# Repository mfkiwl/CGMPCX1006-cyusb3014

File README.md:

# CGMPCX1006
Amplifier Board PCB Project

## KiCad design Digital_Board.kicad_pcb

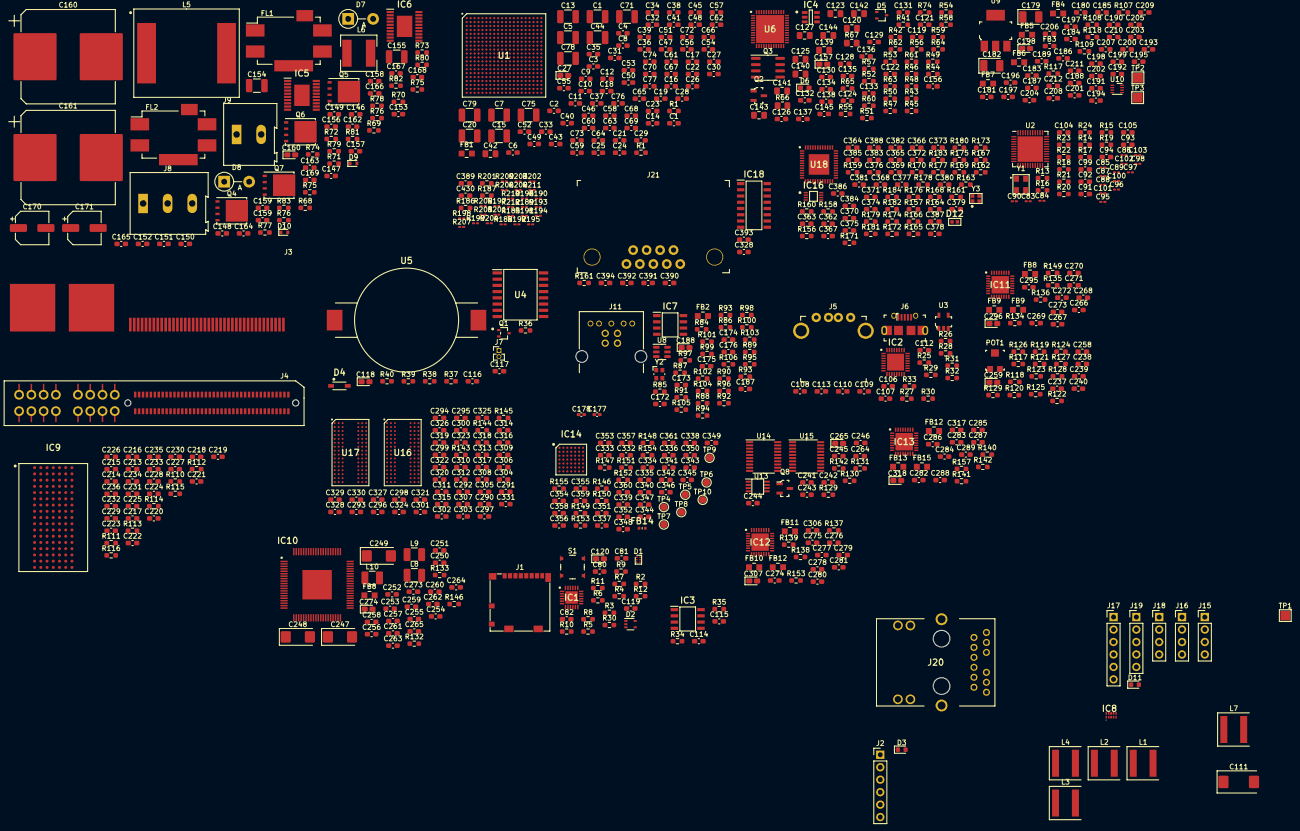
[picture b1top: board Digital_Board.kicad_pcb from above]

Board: 2 copper layers, 761 parts (0 on the bottom side), 493 nets, no tracks yet.

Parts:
C1, C5, C7, C13, C15, C20, C71, C75, C78, C79: 100uF; C_1210_3225Metric_Pad1.33x2.70mm_HandSolder
C1#2, C119, C156#2, C159#2, C175, C187#2, C197#2, C258#2, C264#2, C273#2, C295#2, C306#2, C317#2: C_Small; C_0603_1608Metric_Pad1.08x0.95mm_HandSolder
C2, C3, C6, C9, C11, C14, C16, C18, C21, C22, C27, C34, C41, C57, C62, C63, C67, C68, C69, C70, C72, C73, C74, C76, C77, C113, C119#2, C180, C186: 4.7uF; C_0603_1608Metric_Pad1.08x0.95mm_HandSolder
C4, C8, C10, C12, C17, C19, C23, C24, C25, C26, C28, C29, C30, C31, C32, C33, C35, C36, C37, C38, C39, C40, C43, C45, C46, C47, C48, C49, C50, C51, C52, C53, C54, C55, C56, C58, C59, C60, C61, C64, C65, C66, C314, C315, C318, C319, C322, C323: 470nF; C_0603_1608Metric_Pad1.08x0.95mm_HandSolder
C27#2, C120, C157#2, C160#2, C188#2, C198#2, C259#2, C265#2, C274#2, C296#2, C307#2, C318#2: C_Polarized_Small; CP_EIA-1608-10_AVX-L_Pad1.25x1.05mm_HandSolder
C42, C120#2, C123, C125, C127: 10uF; C_0805_2012Metric_Pad1.18x1.45mm_HandSolder
C44: 47uF; C_1210_3225Metric_Pad1.33x2.70mm_HandSolder
C80, C81, C82, C106, C107, C108, C109, C110, C114, C117, C124, C135, C136, C137, C138, C146, C147, C152, C153, C164, C165, C174, C176, C181, C183, C184, C185, C187, C189, C190, C191, C193, C194, C195, C196, C198, C199, C200, C201, C202, C203, C204, C205, C211, C213, C214, C215, C216, C217, C218, C219, C220, C221, C222, C223, C224, C225, C226, C227, C228, C229, C230, C231, C232, C233, C234, C235, C236, C237, C241, C242, C243, C244, C245, C246, C250, C251, C252, C253, C254, C255, C256, C257, C258, C259, C260, C261, C262, C263, C264, C265, C266, C270, C271, C272, C273, C274, C278, C279, C280, C281, C282, C286, C287, C288, C289, C389, C390, C391, C392, C393, C394: 100nF; C_0603_1608Metric_Pad1.08x0.95mm_HandSolder
C83, C84, C85, C86, C87, C88, C89, C90, C95, C96, C97, C98, C100, C101, C102, C103: 100nF; C_0201_0603Metric_Pad0.64x0.40mm_HandSolder
C91, C92, C93, C94, C99, C104, C105, C126, C128, C134, C145, C166, C167, C335, C338, C339, C343, C362, C363, C364, C365, C366, C367, C368: 1uF; C_0603_1608Metric_Pad1.08x0.95mm_HandSolder
C111: 150uF; CP_EIA-7343-30_AVX-N
C112: 1nF; C_0603_1608Metric_Pad1.08x0.95mm_HandSolder
C115: 30pF; C_0603_1608Metric_Pad1.08x0.95mm_HandSolder
C116, C346, C369, C370, C371, C372, C373, C374, C375, C376, C377, C378, C379, C380, C384, C385, C386, C387, C388: 0.1uF; C_0603_1608Metric_Pad1.08x0.95mm_HandSolder
C118: 1uF; CP_EIA-1608-10_AVX-L_Pad1.25x1.05mm_HandSolder
C121, C133: 1uFF; C_0603_1608Metric_Pad1.08x0.95mm_HandSolder
C122: 2.2nF; C_0603_1608Metric_Pad1.08x0.95mm_HandSolder
C129, C130, C131, C132: 2.7nF; C_0603_1608Metric_Pad1.08x0.95mm_HandSolder
C139, C140, C141, C142: 47uF; C_0805_2012Metric_Pad1.18x1.45mm_HandSolder
C143, C144: 22uF; C_0805_2012Metric_Pad1.18x1.45mm_HandSolder
C148, C149, C150, C151, C188, C192, C197: 2.2uF; C_0603_1608Metric_Pad1.08x0.95mm_HandSolder
C154, C155: 1uF; C_1210_3225Metric_Pad1.33x2.70mm_HandSolder
C156: 560pF; C_0603_1608Metric_Pad1.08x0.95mm_HandSolder
C157: 200pF; C_0603_1608Metric_Pad1.08x0.95mm_HandSolder
C158, C159, C353: 33nF; C_0603_1608Metric_Pad1.08x0.95mm_HandSolder
C160, C161: 330uF; CP_Elec_18x17.5
C162, C163: 10pF; C_0603_1608Metric_Pad1.08x0.95mm_HandSolder
C168: 220pF; C_0603_1608Metric_Pad1.08x0.95mm_HandSolder
C169: 270pF; C_0603_1608Metric_Pad1.08x0.95mm_HandSolder
C170, C171: 47uF; CP_Elec_6.3x5.9
C172, C173: 7pF; C_0603_1608Metric_Pad1.08x0.95mm_HandSolder
C177, C178: 100nF; C_0402_1005Metric_Pad0.74x0.62mm_HandSolder
C179, C182: 10uF; CP_EIA-3528-21_Kemet-B_Pad1.50x2.35mm_HandSolder
C206, C207, C208, C209, C210, C212, C292, C297, C330, C331: 10nF; C_0603_1608Metric_Pad1.08x0.95mm_HandSolder
C238, C240: 900pF; C_0603_1608Metric_Pad1.08x0.95mm_HandSolder
C239: 4.7pF; C_0603_1608Metric_Pad1.08x0.95mm_HandSolder
C247, C248, C249: 100uF; CP_EIA-6032-28_Kemet-C
C267, C268, C269, C275, C276, C277, C283, C284, C285, C332, C341, C342, C345, C347, C348, C350, C383: 10uF; C_0603_1608Metric_Pad1.08x0.95mm_HandSolder
C290, C291, C293, C294, C295, C296, C298, C299, C300, C301, C302, C303, C304, C305, C306, C307, C308, C309, C310, C311, C312, C313, C316, C317, C320, C321, C324, C325, C326, C327, C328, C329: 47nF; C_0603_1608Metric_Pad1.08x0.95mm_HandSolder
C328#2, C430: aaaa; C_0603_1608Metric_Pad1.08x0.95mm_HandSolder
C333, C334, C336, C337, C340, C344, C349, C351: 47uF; C_0603_1608Metric_Pad1.08x0.95mm_HandSolder
C352: 15nF; C_0603_1608Metric_Pad1.08x0.95mm_HandSolder
C354, C355, C356, C357, C358, C359, C360, C361: 4.7nF; C_0603_1608Metric_Pad1.08x0.95mm_HandSolder
C381, C382: 8pF; C_0603_1608Metric_Pad1.08x0.95mm_HandSolder
D1: PESD5V0L5UF; SOT-886
D2: SP0504BAJT; SOT-353_SC-70-5
D3, D11: LED_Small; LED_0603_1608Metric
D4: B0520LW-7-F; SOD3716X145N
D5: BAS16W; SOT-323_SC-70
D6: LED; LED_0603_1608Metric_Pad1.05x0.95mm_HandSolder
D7, D8: SAC50; D_DO-15_P5.08mm_Vertical_AnodeUp
D9, D10: BAS516; D_SOD-523
D12: GREEN; LEDC1006X25N
FB1, FB4, FB5, FB6, FB7, FB8, FB8#2, FB9, FB9#2, FB10, FB11, FB12, FB12#2, FB13, FB15: MPZ2012S601AT000; 0805
FB2: BLM21PG221SN1D; 0805
FB3: BLM18SG121TZ1D; L_0603_1608Metric_Pad1.05x0.95mm_HandSolder
FB14: 1.2A; BEADC1005X55N
FL1: BNX025; Filter_Murata_BNX025
FL2: BNX024; Filter_Murata_BNX024
IC1: TXS02612RTWR; QFN50P400X400X80-25N-D
IC2: USB3320C-EZK; QFN50P500X500X100-33N-D
IC3, IC7: M24M02-DRMN6TP; SOIC127P600X175-8N
IC4: ADR127BUJZ-REEL7; SOT95P280X100-6N
IC5, IC6: LM5116MHX_NOPB; SOP65P640X110-21N
IC8: TPD4E05U06QDQARQ1; DQA_R-PUSON-N10_
IC9: CY7C1062GE30-10BGXI; BGA119C127P7X17_1400X2200X240
IC10: AD9726BSVZ; QFP50P1400X1400X120-81N
IC11, IC12, IC13: LTC2387CUH-18#PBF; QFN50P500X500X80-33N-D
IC14: LTM8078IY#PBF; BGA49C80P7X7_625X625X242
IC16: SN74LVC3G14DCUR; SOP50P310X90-8N
IC18: SP3232EEN-L_TR; SOIC127P600X175-16N
J1: 104031-0811; microSD_HC_Molex_104031-0811
J2, J17: Conn_01x06; PinHeader_1x06_P2.54mm_Vertical
J3: BoardEdge_of_HSEC8-140-01-L-PV-4-1
J4: BoardEdge_of_HSEC8-140-01-L-PV-4-1; HSEC8-140-01-L-PV-4-1
J5: UE27AC54100; USB_A_Female_UE27AC54100
J6: 0475890001; USB_Micro_AB_Female_0475890001
J7: Conn_01x02; PinHeader_1x02_P1.27mm_Vertical
J8: Screw_Terminal_01x03; TerminalBlock_Altech_AK300-3_P5.00mm
J9: Screw_Terminal_01x02; TerminalBlock_Altech_AK300-2_P5.00mm
J11: USB3_B; GSB3211311WEU
J15, J16, J18: Conn_01x04; PinHeader_1x04_P2.54mm_Vertical
J19: Conn_01x05; PinHeader_1x05_P2.54mm_Vertical
J20: RJMG2012211A0FR
J21: 5747840-6; DSUB-9_Jack_5747840-3
L1: 3.3uH; L_Coilcraft_XAL60xx_6.36x6.56mm
L2, L7: 1uH; L_Coilcraft_XAL60xx_6.36x6.56mm
L3, L4: 6.8uH; L_Coilcraft_XAL60xx_6.36x6.56mm
L5: 3.3uH; IHLP6767GZER3R3M01
L6: 2.2uH; L_Coilcraft_XxL7070
L8, L9, L10: 10uH; L_1210_3225Metric_Pad1.42x2.65mm_HandSolder
POT1: TC33X-2-103E; Trimpot_3.8mmx3.6mm_TC33X-2-103E
Q1: MCH3481-TL-W; SOT65P270X085-3N
Q2, Q8: FDV301N; SOT-23-3
Q3: FDS9926A; SOIC-8_3.9x4.9mm_P1.27mm
Q4, Q6: CSD18534Q5A; TDSON-8-1
Q5, Q7: CSD18540Q5B; TDSON-8-1
R1, R3, R31, R32, R34, R51, R54, R99, R102, R110, R111, R112, R161, R162, R163: 0; R_0603_1608Metric_Pad0.98x0.95mm_HandSolder
R1#2, R30#2, R74#2, R75#2, R76#2, R93#2, R117#2, R118#2, R129#2, R142#2, R146#2, R149#2, R153#2, R157#2: R_Small_US; R_0603_1608Metric_Pad0.98x0.95mm_HandSolder
R2, R9, R10, R15, R18, R42, R48, R107, R144: 4.7K; R_0603_1608Metric_Pad0.98x0.95mm_HandSolder
R4, R6, R13, R14, R16, R17, R19, R20, R40, R41, R44, R84, R85, R100, R113, R114, R115, R129, R130, R134, R135, R136, R137, R138, R139, R140, R141, R142, R148, R149, R159: 10K; R_0603_1608Metric_Pad0.98x0.95mm_HandSolder
R5, R105: 200; R_0603_1608Metric_Pad0.98x0.95mm_HandSolder
R7, R8, R21, R22, R23, R24, R122, R123, R127, R128: 100; R_0603_1608Metric_Pad0.98x0.95mm_HandSolder
R11, R12: 220; R_0603_1608Metric_Pad0.98x0.95mm_HandSolder
R25, R153: 1.5K; R_0603_1608Metric_Pad0.98x0.95mm_HandSolder
R26, R43: 8.06K; R_0603_1608Metric_Pad0.98x0.95mm_HandSolder
R27, R29, R45, R101: 100K; R_0603_1608Metric_Pad0.98x0.95mm_HandSolder
R28, R30, R36, R37, R38, R39, R120, R121, R126, R133, R146, R147: 1K; R_0603_1608Metric_Pad0.98x0.95mm_HandSolder
R33, R74, R75, R119, R154, R155: 1M; R_0603_1608Metric_Pad0.98x0.95mm_HandSolder
R35: 4K; R_0603_1608Metric_Pad0.98x0.95mm_HandSolder
R46, R131: 680; R_0603_1608Metric_Pad0.98x0.95mm_HandSolder
R47, R77: 66.5K; R_0603_1608Metric_Pad0.98x0.95mm_HandSolder
R49: 8.87K; R_0603_1608Metric_Pad0.98x0.95mm_HandSolder
R50: 20K; R_0603_1608Metric_Pad0.98x0.95mm_HandSolder
R52, R53: 47K; R_0603_1608Metric_Pad0.98x0.95mm_HandSolder
R55: 39.2K; R_0603_1608Metric_Pad0.98x0.95mm_HandSolder
R56: 12.7K 1%; R_0603_1608Metric_Pad0.98x0.95mm_HandSolder
R57: 4.99K 1%; R_0603_1608Metric_Pad0.98x0.95mm_HandSolder
R58: 1.91K 1%; R_0603_1608Metric_Pad0.98x0.95mm_HandSolder
R59: 2.49K 1%; R_0603_1608Metric_Pad0.98x0.95mm_HandSolder
R60: 19.6K 1%; R_0603_1608Metric_Pad0.98x0.95mm_HandSolder
R61: 10.2K; R_0603_1608Metric_Pad0.98x0.95mm_HandSolder
R62: 31.6K 1%; R_0603_1608Metric_Pad0.98x0.95mm_HandSolder
R63: 28.7K 1%; R_0603_1608Metric_Pad0.98x0.95mm_HandSolder
R64: 10.2K 1%; R_0603_1608Metric_Pad0.98x0.95mm_HandSolder
R65: 10K 1%; R_0603_1608Metric_Pad0.98x0.95mm_HandSolder
R66, R67: 0R; R_0805_2012Metric_Pad1.20x1.40mm_HandSolder
R68, R70: 52.3K; R_0603_1608Metric_Pad0.98x0.95mm_HandSolder
R69, R71: 1.74K; R_0603_1608Metric_Pad0.98x0.95mm_HandSolder
R72, R81: 9.76K; R_0603_1608Metric_Pad0.98x0.95mm_HandSolder
R73: 5.23K; R_0603_1608Metric_Pad0.98x0.95mm_HandSolder
R76: 133K; R_0603_1608Metric_Pad0.98x0.95mm_HandSolder
R78: 2mOhm; R_0603_1608Metric_Pad0.98x0.95mm_HandSolder
R79: 6mOhm; R_0603_1608Metric_Pad0.98x0.95mm_HandSolder
R80: 86.6K; R_0603_1608Metric_Pad0.98x0.95mm_HandSolder
R82: 32.4K; R_0603_1608Metric_Pad0.98x0.95mm_HandSolder
R83: 10.4K; R_0603_1608Metric_Pad0.98x0.95mm_HandSolder
R86, R87, R88, R89, R90, R91, R92, R93, R94, R95, R96, R97, R98, R157, R160: 22; R_0603_1608Metric_Pad0.98x0.95mm_HandSolder
R103, R104, R116, R132: 2K; R_0603_1608Metric_Pad0.98x0.95mm_HandSolder
R106: 6.04K; R_0603_1608Metric_Pad0.98x0.95mm_HandSolder
R108, R109: 0R; R_0603_1608Metric_Pad0.98x0.95mm_HandSolder
R117, R118, R124, R125: Select; R_0603_1608Metric_Pad0.98x0.95mm_HandSolder
R143, R145: 240; R_0603_1608Metric_Pad0.98x0.95mm_HandSolder
R150: 28K; R_0603_1608Metric_Pad0.98x0.95mm_HandSolder
R151: 665K; R_0603_1608Metric_Pad0.98x0.95mm_HandSolder
R152: 118K; R_0603_1608Metric_Pad0.98x0.95mm_HandSolder
R156: 11K; R_0603_1608Metric_Pad0.98x0.95mm_HandSolder
R158: 2.2K; R_0603_1608Metric_Pad0.98x0.95mm_HandSolder
R161#2, R201#2: AAA; R_0603_1608Metric_Pad0.98x0.95mm_HandSolder
R164, R181, R182: 420; R_0603_1608Metric_Pad0.98x0.95mm_HandSolder
R165, R166, R167, R168, R169, R170, R171, R172, R173, R174, R175, R176, R177, R178, R179, R180, R183, R184: 2.49K; R_0603_1608Metric_Pad0.98x0.95mm_HandSolder
R185: 40.2; R_0201_0603Metric_Pad0.64x0.40mm_HandSolder
R186, R187: 80.6; R_0603_1608Metric_Pad0.98x0.95mm_HandSolder
R188, R189, R190, R191, R192, R193, R194, R195, R196, R197, R198, R199, R200, R201, R202, R203, R204, R205, R206, R207, R208, R209, R210, R212: 10; R_0201_0603Metric_Pad0.64x0.40mm_HandSolder
R211: 80.6; R_0201_0603Metric_Pad0.64x0.40mm_HandSolder
S1: TL3315NF100Q; Switch_Tactile_SMD_4.5x4.5mm_TL3315NF160Q
TP1, TP2, TP3: TestPoint; TestPoint_Pad_2.0x2.0mm
TP4, TP5, TP6, TP7, TP8, TP9, TP10: TestPoint; TestPoint_Pad_D1.5mm
U1: XA7Z020-1CLG400Q; BGA400C80P20X20_1700X1700X160
U2: Si5344A-D; QFN-44-1EP_7x7mm_P0.5mm_EP5.2x5.2mm
U3: TPS2051BDBVR; SOT-753
U4: DS3231S#; SOIC127P1032X265-16N
U5: BU2032SM-HD-G
U6: ADP5052ACPZ-R7; QFN50P700X700X80-49N-D
U8: WE-TVS-82400102; SOT-23-6
U9: NCP1117ST33T3G; SOT-223
U10: MIC23150; TDFN-8-2x2mm_P0.5mm
U13: TCA9406DC; SOP65P425X315X130-8N
U14, U15: TXS0108EPW; TSSOP-20_4.4x6.5mm_P0.65mm
U16, U17: AS4C256M16D3LC-12BCN; BGA96C80P9X16_750X1350X120
U18: DP83869HMRGZT; QFN50P700X700X100-49N-D
Y1: CX3225SB48000D0FPJC1; OSCCC320X250X60N
Y2: 19.2Mhz; Crystal_SMD_Abracon_ABM10-4Pin_2.5x2.0mm
Y3: XRCGE25M000FBA1AR0

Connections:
5VUSB3: C179.1, C180.1, FB3.1, R102.1, R107.2, U8.5, U9.3, U10.6, U10.7
+48VIN: C155.1, D7.1, FL2.1, J4.81, J4.82, J8.3
+48VIN_F: C146.1, C147.1, C148.1, C149.1, C150.1, C151.1, C152.1, C153.1, C161.1, FL2.2, IC5.1, IC6.1, Q4.5, Q6.5, R68.1, R70.1, R74.1, R75.1
-48VIN: J3.81, J3.82, J8.1
/12V: C120#2.1, C123.1, C125.1, C127.1, C160.1, C170.1, D4.1, FL1.2, IC5.10, J7.1, L5.1, R80.1, U6.4, U6.9, U6.24, U6.25, U6.35, U6.36
/48V_12V_Buck/EXT_12VIN: C154.1, D8.1, FL1.1, J9.2
/48V_12V_Buck/EXT_12VIN_G: C154.2, D8.2, FL1.3, J9.1
/ADC/ADC_CNV_N: IC11.27, IC12.27, IC13.27
/ADC/ADC_CNV_P: IC11.28, IC12.28, IC13.28
/BTB_Connector/ADC1_CLK_N: J4.53, U1.W9
/BTB_Connector/ADC1_CLK_P: J4.51, U1.W10
/BTB_Connector/ADC1_DA_N: J4.65, U1.Y11
/BTB_Connector/ADC1_DA_P: J4.63, U1.W11
/BTB_Connector/ADC1_DCO_N: J4.59, U1.U8
/BTB_Connector/ADC1_DCO_P: J4.57, U1.U9
/BTB_Connector/ADC2_CLK_N: J4.71, U1.U5
/BTB_Connector/ADC2_CLK_P: J4.69, U1.T5
/BTB_Connector/ADC2_DA_N: J4.76, U1.V10
/BTB_Connector/ADC2_DA_P: J4.78, U1.V11
/BTB_Connector/ADC2_DCO_N: J4.77, U1.Y13
/BTB_Connector/ADC2_DCO_P: J4.75, U1.Y12
/BTB_Connector/ADC3_CLK_N: J4.70, U1.V7
/BTB_Connector/ADC3_CLK_P: J4.72, U1.U7
/BTB_Connector/ADC3_DA_N: J4.58, U1.W6
/BTB_Connector/ADC3_DA_P: J4.60, U1.V6
/BTB_Connector/ADC3_DCO_N: J4.64, U1.Y8
/BTB_Connector/ADC3_DCO_P: J4.66, U1.Y9
/BTB_Connector/ADC_CNV_N: J4.52, U1.W8
/BTB_Connector/ADC_CNV_P: J4.54, U1.V8
/BTB_Connector/FDAC_DB0_N: J4.45, U1.P20
/BTB_Connector/FDAC_DB0_P: J4.47, U1.N20
/BTB_Connector/FDAC_DB1_N: J4.39, U1.U15
/BTB_Connector/FDAC_DB1_P: J4.41, U1.U14
/BTB_Connector/FDAC_DB2_N: J4.33, U1.H15
/BTB_Connector/FDAC_DB2_P: J4.35, U1.G15
/BTB_Connector/FDAC_DB3_N: J4.27, U1.R17
/BTB_Connector/FDAC_DB3_P: J4.29, U1.R16
/BTB_Connector/FDAC_DB4_N: J4.21, U1.R14
/BTB_Connector/FDAC_DB4_P: J4.23, U1.P14
/BTB_Connector/FDAC_DB5_N: J4.15, U1.P16
/BTB_Connector/FDAC_DB5_P: J4.17, U1.P15
/BTB_Connector/FDAC_DB6_N: J4.9, U1.P18
/BTB_Connector/FDAC_DB6_P: J4.11, U1.N17
/BTB_Connector/FDAC_DB7_N: J4.3, U1.W19
/BTB_Connector/FDAC_DB7_P: J4.5, U1.W18
/BTB_Connector/FDAC_DB8_N: J4.48, U1.W13
/BTB_Connector/FDAC_DB8_P: J4.46, U1.V12
/BTB_Connector/FDAC_DB9_N: J4.42, U1.T10
/BTB_Connector/FDAC_DB9_P: J4.40, U1.T11
/BTB_Connector/FDAC_DB10_N: J4.36, U1.J16
/BTB_Connector/FDAC_DB10_P: J4.34, U1.K16
/BTB_Connector/FDAC_DB11_N: J4.30, U1.M15
/BTB_Connector/FDAC_DB11_P: J4.28, U1.M14
/BTB_Connector/FDAC_DB12_N: J4.24, U1.F17
/BTB_Connector/FDAC_DB12_P: J4.22, U1.F16
/BTB_Connector/FDAC_DB13_N: J4.18, U1.D18
/BTB_Connector/FDAC_DB13_P: J4.16, U1.E17
/BTB_Connector/FDAC_DB14_N: J4.12, U1.A20
/BTB_Connector/FDAC_DB14_P: J4.10, U1.B19
/BTB_Connector/FDAC_DB15_N: J4.6, U1.B20
/BTB_Connector/FDAC_DB15_P: J4.4, U1.C20
/Clock_Gen/CLK_A0: R19.2, R20.1, U2.16
/Clock_Gen/CLK_A1: R16.2, R17.1, U2.15
/Clock_Gen/CLK_A_N: C84.1, R21.2, U2.44
/Clock_Gen/CLK_A_P: C83.1, R21.1, U2.43
/Clock_Gen/CLK_B_N: C86.1, R22.2, U2.2
/Clock_Gen/CLK_B_P: C85.1, R22.1, U2.1
/Clock_Gen/CLK_C_N: C88.1, R23.2, U2.11
/Clock_Gen/CLK_C_P: C87.1, R23.1, U2.10
/Clock_Gen/CLK_D_N: C90.1, R24.2, U2.42
/Clock_Gen/CLK_D_P: C89.1, R24.1, U2.41
/Clock_Gen/CLK_I2C_SEL: R13.2, R14.1, U2.38
/EEPROM/EEPROM_SDA: C115.1, IC3.5, R35.2
/Ethernet/ETH_INT_PDWN: R158.2, U18.44
/Ethernet/ETH_MDC: U1.C10, U18.42
/Ethernet/ETH_MDIO: R153.1, U1.C11, U18.41
/Ethernet/ETH_PHY_CONN/ETH_A_N: J20.8, U18.2
/Ethernet/ETH_PHY_CONN/ETH_A_P: J20.9, U18.1
/Ethernet/ETH_PHY_CONN/ETH_B_N: J20.3, U18.5
/Ethernet/ETH_PHY_CONN/ETH_B_P: J20.2, U18.4
/Ethernet/ETH_PHY_CONN/ETH_C_N: J20.4, U18.8
/Ethernet/ETH_PHY_CONN/ETH_C_P: J20.5, U18.7
/Ethernet/ETH_PHY_CONN/ETH_D_N: J20.11, U18.11
/Ethernet/ETH_PHY_CONN/ETH_D_P: J20.10, U18.10
/Ethernet/ETH_PHY_CONN/ETH_GPIO_0: IC16.6, R163.1, R175.2, R176.1, TP6.1, U18.45
/Ethernet/ETH_PHY_CONN/ETH_JTAG_CLK: TP7.1, U18.21
/Ethernet/ETH_PHY_CONN/ETH_JTAG_TDI: TP8.1, U18.24
/Ethernet/ETH_PHY_CONN/ETH_JTAG_TDO: R157.1, R157.2, R169.2, R170.1, TP9.1, U18.22
/Ethernet/ETH_PHY_CONN/ETH_JTAG_TMS: TP10.1, U18.23
/Ethernet/ETH_PHY_CONN/LED_0: IC16.1, R161.1, R171.2, R172.1, U18.47
/Ethernet/ETH_PHY_CONN/LED_1: IC16.3, R162.1, R173.2, R174.1, U18.46
/Ethernet/ETH_PHY_CONN/LED_P_0: IC16.7, J20.13, R161.2
/Ethernet/ETH_PHY_CONN/LED_P_1: IC16.5, J20.15, R162.2
/Ethernet/ETH_PHY_CONN/LED_P_2: D12.1, IC16.2, R163.2
/Ethernet/ETH_PHY_CONN/RX_D0: R179.2, R180.1
/Ethernet/ETH_PHY_CONN/RX_D1: R183.2, R184.1
/Ethernet/ETH_PHY_CONN/RX_D2: R165.2, R166.1
/Ethernet/ETH_PHY_CONN/RX_D3: R167.2, R168.1
/Ethernet/ETH_RESETn: R159.2, R160.1, U18.43
/Ethernet/ETH_RX_CLK: U1.B17, U18.32
/Ethernet/ETH_RX_CTRL: R177.2, R178.1, U1.D13, U18.38
/Ethernet/ETH_TX_CLK: U1.A19, U18.29
/Ethernet/ETH_TX_CTRL: U1.F14, U18.37
/Ext_Analog/AN0_N: C238.1, R123.1
/Ext_Analog/AN0_P: C238.2, R122.1
/Ext_Analog/AN1_N: C240.1, R128.1
/Ext_Analog/AN1_P: C240.2, R127.1
/FDAC_CLKIN_N: C100.1, J3.75
/FDAC_CLKIN_P: C95.1, J3.77
/FPGA_Banks/DAC_DCLK_IN_N: J3.69, U1.H17
/FPGA_Banks/DAC_DCLK_IN_P: J3.71, U1.H16
/FPGA_Banks/DAC_DCLK_OUT_N: J3.63, U1.K18
/FPGA_Banks/DAC_DCLK_OUT_P: J3.65, U1.K17
/FPGA_Banks/DDR3_A0: R202.1, U16.N3, U17.N3
/FPGA_Banks/DDR3_A1: R201.1, U16.P7, U17.P7
/FPGA_Banks/DDR3_A2: R200.1, U16.P3, U17.P3
/FPGA_Banks/DDR3_A3: R199.1, U16.N2, U17.N2
/FPGA_Banks/DDR3_A4: R198.1, U16.P8, U17.P8
/FPGA_Banks/DDR3_A5: R197.1, U16.P2, U17.P2
/FPGA_Banks/DDR3_A6: R196.1, U16.R8, U17.R8
/FPGA_Banks/DDR3_A7: R195.1, U16.R2, U17.R2
/FPGA_Banks/DDR3_A8: R194.1, U16.T8, U17.T8
/FPGA_Banks/DDR3_A9: R193.1, U16.R3, U17.R3
/FPGA_Banks/DDR3_A10: R192.1, U16.L7, U17.L7
/FPGA_Banks/DDR3_A11: R191.1, U16.R7, U17.R7
/FPGA_Banks/DDR3_A12: R190.1, U16.N7, U17.N7
/FPGA_Banks/DDR3_A13: R189.1, U16.T3, U17.T3
/FPGA_Banks/DDR3_A14: R188.1, U16.T7, U17.T7
/FPGA_Banks/DDR3_BA0: R205.1, U16.M2, U17.M2
/FPGA_Banks/DDR3_BA1: R204.1, U16.N8, U17.N8
/FPGA_Banks/DDR3_BA2: R203.1, U16.M3, U17.M3
/FPGA_Banks/DDR3_CAS: R207.1, U16.K3, U17.K3
/FPGA_Banks/DDR3_CKE0: R210.1, U16.K9, U17.K9
/FPGA_Banks/DDR3_CK_N: R211.2, U1.M2, U16.K7, U17.K7
/FPGA_Banks/DDR3_CK_P: R211.1, U1.L2, U16.J7, U17.J7
/FPGA_Banks/DDR3_CS: R208.1, U16.L2, U17.L2
/FPGA_Banks/DDR3_D0: U1.E3, U16.E3
/FPGA_Banks/DDR3_D1: U1.H2, U16.F7
/FPGA_Banks/DDR3_D2: U1.E2, U16.F2
/FPGA_Banks/DDR3_D3: U1.G3, U16.F8
/FPGA_Banks/DDR3_D4: U1.J1, U16.H3
/FPGA_Banks/DDR3_D5: U1.H3, U16.H8
/FPGA_Banks/DDR3_D6: U1.J3, U16.G2
/FPGA_Banks/DDR3_D7: U1.H1, U16.H7
/FPGA_Banks/DDR3_D8: U1.D3, U16.D7
/FPGA_Banks/DDR3_D9: U1.E1, U16.C3
/FPGA_Banks/DDR3_D10: U1.C1, U16.C8
/FPGA_Banks/DDR3_D11: U1.C3, U16.C2
/FPGA_Banks/DDR3_D12: U1.B3, U16.A7
/FPGA_Banks/DDR3_D13: U1.A2, U16.A2
/FPGA_Banks/DDR3_D14: U1.D1, U16.B8
/FPGA_Banks/DDR3_D15: U1.A4, U16.A3
/FPGA_Banks/DDR3_D16: U1.U4, U17.E3
/FPGA_Banks/DDR3_D17: U1.T4, U17.F7
/FPGA_Banks/DDR3_D18: U1.U3, U17.F2
/FPGA_Banks/DDR3_D19: U1.R1, U17.F8
/FPGA_Banks/DDR3_D20: U1.R3, U17.H3
/FPGA_Banks/DDR3_D21: U1.P3, U17.H8
/FPGA_Banks/DDR3_D22: U1.U2, U17.G2
/FPGA_Banks/DDR3_D23: U1.P1, U17.H7
/FPGA_Banks/DDR3_D24: U1.V2, U17.D7
/FPGA_Banks/DDR3_D25: U1.V3, U17.C3
/FPGA_Banks/DDR3_D26: U1.W3, U17.C8
/FPGA_Banks/DDR3_D27: U1.V1, U17.C2
/FPGA_Banks/DDR3_D28: U1.Y2, U17.A7
/FPGA_Banks/DDR3_D29: U1.Y3, U17.A2
/FPGA_Banks/DDR3_D30: U1.W1, U17.B8
/FPGA_Banks/DDR3_D31: U1.Y4, U17.A3
/FPGA_Banks/DDR3_DM0: U1.F1, U16.E7
/FPGA_Banks/DDR3_DM1: U1.A1, U16.D3
/FPGA_Banks/DDR3_DM2: U1.T1, U17.E7
/FPGA_Banks/DDR3_DM3: U1.Y1, U17.D3
/FPGA_Banks/DDR3_DQS0_N: U1.F2, U16.G3
/FPGA_Banks/DDR3_DQS0_P: U1.G2, U16.F3
/FPGA_Banks/DDR3_DQS1_N: U1.B2, U16.B7
/FPGA_Banks/DDR3_DQS1_P: U1.C2, U16.C7
/FPGA_Banks/DDR3_DQS2_N: U1.T2, U17.G3
/FPGA_Banks/DDR3_DQS2_P: U1.R2, U17.F3
/FPGA_Banks/DDR3_DQS3_N: U1.W4, U17.B7
/FPGA_Banks/DDR3_DQS3_P: U1.W5, U17.C7
/FPGA_Banks/DDR3_ODT0: R212.1, U16.K1, U17.K1
/FPGA_Banks/DDR3_RAS: R206.1, U16.J3, U17.J3
/FPGA_Banks/DDR3_RESET: R144.1, U1.B4, U16.T2, U17.T2
/FPGA_Banks/DDR3_VREF: C292.1, C297.1, C330.1, C331.1, C389.2, U1.H6, U1.P6, U16.H1, U16.M8, U17.H1, U17.M8
/FPGA_Banks/DDR3_WE: R209.1, U16.L3, U17.L3
/FPGA_Banks/ETH_RX_D0: U1.D11, U18.33
/FPGA_Banks/ETH_RX_D1: U1.A16, U18.34
/FPGA_Banks/ETH_RX_D2: U1.F15, U18.35
/FPGA_Banks/ETH_RX_D3: U1.A15, U18.36
/FPGA_Banks/ETH_TX_D0: U1.E14, U18.28
/FPGA_Banks/ETH_TX_D1: U1.B18, U18.27
/FPGA_Banks/ETH_TX_D2: U1.D10, U18.26
/FPGA_Banks/ETH_TX_D3: U1.A17, U18.25
/FPGA_Banks/FX3_PMOD0: R99.1, U1.Y16
/FPGA_Banks/FX3_PMOD1: R85.1, U1.Y17
/FPGA_Banks/USB2_CLK: IC2.1, R27.1, U1.A11
/FPGA_Banks/USB2_DATA0: IC2.3, U1.A14
/FPGA_Banks/USB2_DATA1: IC2.4, U1.D15
/FPGA_Banks/USB2_DATA2: IC2.5, U1.A12
/FPGA_Banks/USB2_DATA3: IC2.6, U1.F12
/FPGA_Banks/USB2_DATA4: IC2.7, U1.C16
/FPGA_Banks/USB2_DATA5: IC2.9, U1.A10
/FPGA_Banks/USB2_DATA6: IC2.10, U1.E13
/FPGA_Banks/USB2_DATA7: IC2.13, U1.C18
/FPGA_Banks/USB2_DIR: IC2.31, U1.C13
/FPGA_Banks/USB2_NXT: IC2.2, U1.E16
/FPGA_Banks/USB2_OC: R30.1, U1.U13, U3.3
/FPGA_Banks/USB2_RESTN: IC2.27, R25.2, U1.D16
/FPGA_Banks/USB2_STP: IC2.29, U1.C15
/FPGA_Config/ESD_CLK: IC1.19, J1.5
/FPGA_Config/ESD_CMD: IC1.20, J1.3
/FPGA_Config/ESD_DAT0: IC1.18, J1.7
/FPGA_Config/ESD_DAT1: IC1.16, J1.8
/FPGA_Config/ESD_DAT2: IC1.23, J1.1
/FPGA_Config/ESD_DAT3: IC1.22, J1.2
/FPGA_Config/SD_CD: D1.1, R4.2
/FPGA_Config/TCK_JTAG: D2.5, J2.4, U1.F9
/FPGA_Config/TDI_JTAG: D2.3, J2.2, U1.G6
/FPGA_Config/TDO_JTAG: D2.4, J2.3, U1.F6
/FPGA_Config/TMS_JTAG: D2.1, J2.1, U1.J6
/FPGA_Config/VP: R6.2, R7.1, U1.K9
/I2C2_SCL: R36.2, U4.16
/I2C2_SDA: R15.2, R37.2, U2.13, U4.15, U13.5
/I2C_SCL: R18.2, U2.14, U13.4
/LED_Comm/CAN_H: J18.3, U15.20
/LED_Comm/CAN_L: J18.4, U15.18
/LED_Comm/LCD_RESET: J19.1, U15.17
/LED_Comm/LCD_RX: J19.4, U15.15
/LED_Comm/LCD_TX: J19.3, U15.16
/LED_Comm/SCL: J16.4, U13.1
/LED_Comm/SDA: J16.3, U13.8
/LED_Comm/SPI_CLK: J17.5, U14.13
/LED_Comm/SPI_MISO: J17.3, U14.15
/LED_Comm/SPI_MOSI: J17.4, U14.14
/LED_Comm/SPI_SS: J17.6, U14.12
/LED_Comm/UART_RX: J15.4, U14.18
/LED_Comm/UART_TX: J15.3, U14.20
/Power_Supply/EN2: R41.1, R42.2, U6.23
/Power_Supply/VREG: R51.2, R54.2, U6.43
/RS232_Port/RS232_RX_IN1: IC18.13, J21.4
/RS232_Port/RS232_RX_IN2: IC18.8, J21.8
/RS232_Port/RS232_TX_OUT1: IC18.14, J21.7
/RS232_Port/RS232_TX_OUT2: IC18.7, J21.3
/RTC_FAN/RTC_OSC_OUT: R39.2, U4.1
/RTC_FAN/RTC_RST: TP1.1, U4.4
/RTC_FAN/RTC_SQW: R38.2, U4.3
/USB2/USB2_3V3: C109.1, IC2.20, IC2.21
/USB2/USB2_5V0: C113.1, J5.1, J6.1, R28.2, R31.1, R32.1
/USB2/USB2_D_N: IC2.19, J5.2, J6.2
/USB2/USB2_D_P: IC2.18, J5.3, J6.3
/USB2/USB2_ID: IC2.23, J6.4
/USB2/USB2_SHIELD: C112.2, J5.SH, J6.SH, R33.2
/USB3/CTL0: R86.2, R110.2
/USB3/CTL1: R92.2, R111.2
/USB3/CTL2: R87.2, R112.2
/USB3/CTL5: IC9.A6, R94.2
/USB3/CTL6: IC9.A5, R89.2
/USB3/CTL7: IC9.A4, R95.2
/USB3/CTL8: IC9.A3, R90.2
/USB3/CTL9: IC9.A2, R96.2
/USB3/CTL10: IC9.U6, R91.2
/USB3/CTL11: IC9.U5, R97.2
/USB3/CTL12: IC9.U3, R98.2
/USB3/I2C_SCL: IC7.6, R103.2
/USB3/I2C_SDA: IC7.5, R104.2
/USB3/RESET_IN: C174.1, R101.2
/USB3/SSRX+: IC8.5, IC8.6, J11.6
/USB3/SSRX-: IC8.4, IC8.7, J11.5
/USB3/SSTX+: C177.2, IC8.2, IC8.9, J11.9
/USB3/SSTX-: C178.2, IC8.1, IC8.10, J11.8
/USB3/USB3D+: J11.3, U8.3
/USB3/USB3D-: J11.2, U8.1
/USB3/XTALIN: C172.1, Y2.1
/USB3/XTALOUT: C173.1, Y2.3
AVDD2V5: C249.1, C253.1, C254.1, C259.1, C260.1, C264.1, C265.1, IC10.1, IC10.3, IC10.62, IC10.64, IC10.77, IC10.79, L10.1
AVDD3V3: C247.1, C250.1, C251.1, C252.1, C256.1, C257.1, C258.1, C263.1, IC10.20, IC10.30, IC10.40, IC10.66, IC10.68, IC10.73, IC10.75, L8.1
DVDD2V5: C248.1, C255.1, C262.1, IC10.9, IC10.52, L9.1
ETH_1V1: C334.1, C337.1, C340.1, C344.1, C348.1, C350.1, C364.1, C367.1, C368.1, C371.1, C375.1, C376.1, C378.1, C379.1, C380.1, IC14.F6, IC14.F7, IC14.G6, IC14.G7, R149.1, U18.6, U18.31, U18.39
ETH_1V8: C338.1, C342.1, C347.1, C349.1, C351.1, C362.1, C365.1, C369.1, C372.1, C374.1, C377.1, FB14.1, R158.1, R159.1, R165.1, R167.1, R169.1, R171.1, R173.1, R175.1, R177.1, R179.1, R183.1, U18.18, U18.30
ETH_2V5: C333.1, C336.1, C341.1, C345.1, C363.1, C366.1, C370.1, C373.1, IC14.F1, IC14.F2, IC14.G1, IC14.G2, R148.1, U18.3, U18.9
GNDD: C1.2, C2.2, C3.2, C4.2, C5.2, C6.2, C7.2, C8.2, C9.2, C10.2, C11.2, C12.2, C13.2, C14.2, C15.2, C16.2, C17.2, C18.2, C19.2, C20.2, C21.2, C22.2, C23.2, C24.2, C25.2, C26.2, C27.2, C28.2, C29.2, C30.2, C31.2, C32.2, C33.2, C34.2, C35.2, C36.2, C37.2, C38.2, C39.2, C40.2, C41.2, C42.2, C43.2, C44.2, C45.2, C46.2, C47.2, C48.2, C49.2, C50.2, C51.2, C52.2, C53.2, C54.2, C55.2, C56.2, C57.2, C58.2, C59.2, C60.2, C61.2, C62.2, C63.2, C64.2, C65.2, C66.2, C67.2, C68.2, C69.2, C70.2, C71.2, C72.2, C73.2, C74.2, C75.2, C76.2, C77.2, C78.2, C79.2, C80.2, C81.2, C82.2, C91.2, C92.2, C93.2, C94.2, C99.2, C104.2, C105.2, C106.2, C107.2, C108.2, C109.2, C110.2, C111.2, C112.1, C113.2, C114.1, C115.2, C116.2, C117.2, C118.2, C119#2.2, C120#2.2, C121.2, C122.2, C123.2, C124.2, C125.2, C126.2, C127.2, C128.2, C129.2, C130.2, C131.2, C132.2, C133.2, C134.2, C139.2, C140.2, C141.2, C142.2, C143.2, C144.2, C145.2, C146.2, C147.2, C148.2, C149.2, C150.2, C151.2, C152.2, C153.2, C156.2, C157.2, C158.2, C159.2, C160.2, C161.2, C166.2, C167.2, C170.2, C171.2, C172.2, C173.2, C174.2, C175.2, C176.2, C179.2, C180.2, C181.2, C182.2, C183.2, C184.2, C185.2, C186.2, C187.2, C188.2, C189.2, C190.2, C191.2, C192.2, C193.2, C194.2, C195.2, C196.2, C197.2, C198.2, C199.2, C200.2, C201.2, C202.2, C203.2, C204.2, C205.2, C206.2, C207.2, C208.2, C209.2, C210.2, C211.2, C212.2, C213.2, C214.2, C215.2, C216.2, C217.2, C218.2, C219.2, C220.2, C221.2, C222.2, C223.2, C224.2, C225.2, C226.2, C227.2, C228.2, C229.2, C230.2, C231.2, C232.2, C233.2, C234.2, C235.2, C236.2, C237.2, C239.2, C241.2, C242.2, C243.2, C244.2, C245.2, C246.2, C247.2, C248.2, C249.2, C250.2, C251.2, C252.2, C253.2, C254.2, C255.2, C256.2, C257.2, C258.2, C259.2, C260.2, C261.2, C262.2, C263.2, C264.2, C265.2, C266.2, C267.2, C268.2, C269.2, C270.2, C271.2, C272.2, C273.2, C274.2, C275.2, C276.2, C277.2, C278.2, C279.2, C280.2, C281.2, C282.2, C283.2, C284.2, C285.2, C286.2, C287.2, C288.2, C289.2, C290.2, C291.2, C292.2, C293.2, C294.2, C295.2, C296.2, C298.2, C299.2, C300.2, C301.2, C302.2, C303.2, C304.2, C305.2, C306.2, C307.2, C308.2, C309.2, C310.2, C311.2, C312.2, C313.2, C314.2, C315.2, C316.2, C317.2, C318.2, C319.2, C320.2, C321.2, C322.2, C323.2, C324.2, C325.2, C326.2, C327.2, C328.2, C329.2, C330.2, C332.2, C333.2, C334.2, C335.2, C336.2, C337.2, C338.2, C339.2, C340.2, C341.2, C342.2, C343.2, C344.2, C345.2, C346.2, C347.2, C348.2, C349.2, C350.2, C351.2, C352.2, C353.2, C354.1, C355.1, C356.1, C357.1, C358.1, C359.1, C360.1, C361.1, C362.2, C363.2, C364.2, C365.2, C366.2, C367.2, C368.2, C369.2, C370.2, C371.2, C372.2, C373.2, C374.2, C375.2, C376.2, C377.2, C378.2, C379.2, C380.2, C381.2, C382.2, C383.2, C384.2, C385.2, C386.2, C387.2, C388.2, C389.1, C392.1, C393.1, C394.1, D1.2, D2.2, D3.1, FB2.2, FL1.4, FL2.4, IC1.2, IC1.11, IC1.25, IC2.8, IC2.14, IC2.33, IC3.1, IC3.2, IC3.4, IC4.2, IC5.6, IC5.14, IC5.17, IC5.21, IC6.6, IC6.14, IC6.17, IC6.21, IC7.4, IC8.3, IC8.8, IC9.D3, IC9.D4, IC9.D5, IC9.E2, IC9.E4, IC9.E6, IC9.F3, IC9.F4, IC9.F5, IC9.G2, IC9.G4, IC9.G6, IC9.H3, IC9.H4, IC9.H5, IC9.J2, IC9.J4, IC9.J6, IC9.K3, IC9.K4, IC9.K5, IC9.L2, IC9.L4, IC9.L6, IC9.M3, IC9.M4, IC9.M5, IC9.N2, IC9.N4, IC9.N6, IC9.P3, IC9.P4, IC9.P5, IC10.4, IC10.7, IC10.8, IC10.21, IC10.31, IC10.41, IC10.53, IC10.61, IC10.63, IC10.65, IC10.67, IC10.69, IC10.72, IC10.74, IC10.76, IC10.78, IC10.80, IC10.81, IC11.1, IC11.4, IC11.5, IC11.6, IC11.10, IC11.21, IC11.26, IC11.29, IC11.33, IC12.1, IC12.4, IC12.5, IC12.6, IC12.10, IC12.21, IC12.26, IC12.29, IC12.33, IC13.1, IC13.4, IC13.5, IC13.6, IC13.10, IC13.21, IC13.26, IC13.29, IC13.33, IC14.A1, IC14.A7, IC14.B2, IC14.B3, IC14.B4, IC14.B5, IC14.C2, IC14.C3, IC14.C4, IC14.C5, IC14.D2, IC14.D3, IC14.D4, IC14.D5, IC14.E1, IC14.E2, IC14.E3, IC14.E4, IC14.E5, IC14.E6, IC14.F3, IC14.F4, IC14.F5, IC14.G3, IC14.G4, IC14.G5, IC16.4, IC18.15, J1.6, J2.5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
GNDPWR: C155.2, D7.2, FL2.3, J3.3, J3.7, J3.15, J3.83, J3.84, J4.1, J4.2, J4.7, J4.8, J4.13, J4.14, J4.19, J4.20, J4.25, J4.26, J4.31, J4.32, J4.37, J4.38, J4.43, J4.44, J4.49, J4.50, J4.55, J4.56, J4.61, J4.62, J4.67, J4.68, J4.73, J4.74, J4.79, J4.80, J4.83, J4.84, J8.2
GND_ES: C354.2, C355.2, C356.2, C357.2, C358.2, C359.2, C360.2, C361.2, J20.17, J20.18, R154.2, R155.2
unnamed: C95.2, U2.20
unnamed: C96.2, U2.25
unnamed: C97.2, U2.31
unnamed: C98.2, U2.36
unnamed: C100.2, U2.19
unnamed: C101.2, U2.24
unnamed: C102.2, U2.30
unnamed: C103.2, U2.35
unnamed: C111.1, R32.2
unnamed: C117.1, Q1.2, R40.2
unnamed: C118.1, D4.2, J7.2, Q1.3
unnamed: C122.1, R43.1, R44.2, U6.5, U6.37, U6.48
unnamed: C128.1, U6.42
unnamed: C129.1, R47.2
unnamed: C130.1, R48.2
unnamed: C131.1, R49.2
unnamed: C132.1, R50.2
unnamed: C134.1, R51.1, U6.44
unnamed: C135.1, U6.32
unnamed: C135.2, L1.2, Q3.5, Q3.6, U6.33, U6.34
unnamed: C136.1, L2.2, Q3.7, Q3.8, U6.26, U6.27
unnamed: C136.2, U6.28
unnamed: C137.1, U6.1
unnamed: C137.2, L3.2, U6.3
unnamed: C138.2, L4.2, U6.10
unnamed: C139.1, C141.1, L1.1, R62.1, R66.2
unnamed: C140.1, C142.1, L2.1, R59.1, R67.2
unnamed: C156.1, IC5.5
unnamed: C157.1, IC6.5
unnamed: C158.1, IC5.7
unnamed: C159.1, IC6.7
unnamed: C162.1, C168.1, IC5.8, R80.2, R81.1
unnamed: C162.2, IC5.9, R76.2
unnamed: C163.1, C169.1, IC6.8, R82.2, R83.1
unnamed: C163.2, IC6.9, R77.2
unnamed: C164.1, D9.1, IC5.18
unnamed: C164.2, IC5.20, L5.2, Q4.1, Q4.2, Q4.3, Q5.5
unnamed: C165.1, D10.1, IC6.18
unnamed: C165.2, IC6.20, L6.2, Q6.1, Q6.2, Q6.3, Q7.5
unnamed: C166.1, D9.2, IC5.16
unnamed: C167.1, D10.2, IC6.16
unnamed: C168.2, R76.1
unnamed: C169.2, R77.1
unnamed: C175.1, FB2.1
unnamed: C188.1, C190.1, FB4.2
unnamed: C192.1, C194.1, FB5.2
unnamed: C197.1, C199.1, FB6.2
unnamed: C204.1, C210.1, FB7.1
unnamed: C237.1, POT1.2
unnamed: C239.1, R126.1
unnamed: C261.1, IC10.59
unnamed: C266.1, IC11.32
unnamed: C267.1, IC11.7, IC11.8
unnamed: C268.1, C271.1, FB8.2, IC11.11, IC11.12
unnamed: C270.1, IC11.9
unnamed: C273.1, FB9.2, IC11.22
unnamed: C274.1, IC12.32
unnamed: C275.1, IC12.7, IC12.8
unnamed: C276.1, C279.1, FB10.2, IC12.11, IC12.12
unnamed: C278.1, IC12.9
unnamed: C281.1, FB11.2, IC12.22
unnamed: C282.1, IC13.32
unnamed: C283.1, IC13.7, IC13.8
unnamed: C284.1, C287.1, FB12.2, IC13.11, IC13.12
unnamed: C286.1, IC13.9
unnamed: C289.1, FB13.2, IC13.22
unnamed: C352.1, IC14.A6
unnamed: C353.1, IC14.B6
unnamed: C381.1, U18.20, Y3.1
unnamed: C382.1, U18.19, Y3.3
unnamed: C383.1, R160.2
unnamed: C385.1, J20.12
unnamed: C386.1, J20.6
unnamed: C387.1, J20.1
unnamed: C388.1, J20.7
unnamed: C390.1, IC18.3
unnamed: C390.2, IC18.1
unnamed: C391.1, IC18.5
unnamed: C391.2, IC18.4
unnamed: C393.2, IC18.2
unnamed: C394.2, IC18.6
unnamed: D3.2, R12.2
unnamed: D6.1, R46.2
unnamed: D11.1, R131.1
unnamed: D12.2, R164.2
unnamed: IC1.17, R3.2
unnamed: IC1.24, R2.1
unnamed: IC2.17, R29.1, U3.4
unnamed: IC2.22, R28.1
unnamed: IC2.24, R26.1
unnamed: IC3.3, R34.2
unnamed: IC5.2, R68.2, R69.1
unnamed: IC5.3, R72.1
unnamed: IC5.4, R74.2
unnamed: IC5.11, IC5.13, R78.2
unnamed: IC5.12, Q5.1, Q5.2, Q5.3, R78.1
unnamed: IC5.15, Q5.4
unnamed: IC5.19, Q4.4
unnamed: IC6.2, R70.2, R71.1
unnamed: IC6.3, R73.1
unnamed: IC6.4, R75.2
unnamed: IC6.11, IC6.13, R79.2
unnamed: IC6.12, Q7.1, Q7.2, Q7.3, R79.1
unnamed: IC6.15, Q7.4
unnamed: IC6.19, Q6.4
unnamed: IC9.B2, IC9.B3, IC9.B5, IC9.B6, IC9.C2, IC9.C3, IC9.C5, IC9.C6, IC9.R2, IC9.R3, IC9.R5, IC9.R6, IC9.T2, IC9.T3, IC9.T5, IC9.T6, IC9.U2, R116.1
unnamed: IC9.B4, R110.1, R113.2
unnamed: IC9.T4, R111.1, R114.2
unnamed: IC9.U4, R112.1, R115.2
unnamed: IC10.2, R133.1
unnamed: IC10.60, R132.1
unnamed: IC11.13, R134.2
unnamed: IC11.14, R135.2
unnamed: IC11.25, R136.2
unnamed: IC12.13, R137.2
unnamed: IC12.14, R138.2
unnamed: IC12.25, R139.2
unnamed: IC13.13, R140.2
unnamed: IC13.14, R141.2
unnamed: IC13.25, R142.2
unnamed: IC14.A2, R149.2, TP5.1
unnamed: IC14.B1, R148.2, TP4.1
unnamed: IC14.B7, R150.2
unnamed: IC14.C1, R146.2, R147.2
unnamed: IC14.C6, IC14.D6
unnamed: IC14.C7, R151.2
unnamed: IC14.D7, R152.1
unnamed: J1.9, R5.1
unnamed: J11.1, R102.2
unnamed: R118.1, R123.2
unnamed: R125.1, R128.2
unnamed: J20.14, R181.1
unnamed: J20.16, R182.1
unnamed: L7.2, U10.1, U10.2
unnamed: POT1.1, R120.2
unnamed: POT1.3, R121.2
unnamed: Q2.3, R46.1
unnamed: Q3.2, R53.2, U6.29
unnamed: Q3.4, R52.2, U6.31
unnamed: Q8.1, R129.1, R130.2
unnamed: Q8.3, R131.2
unnamed: R1.2, U1.F11
unnamed: R7.2, R8.1, U1.L10
unnamed: R9.2, S1.1, S1.2, U1.L6
unnamed: R10.2, U1.R10
unnamed: R11.2, R12.1, U1.R11
unnamed: R31.2, U3.1
unnamed: R47.1, U6.39
unnamed: R48.1, U6.22
unnamed: R49.1, U6.46
unnamed: R50.1, U6.15
unnamed: R55.2, U6.41
unnamed: R56.2, U6.16
unnamed: R57.2, R58.2, U6.6
unnamed: R59.2, R65.2, U6.21
unnamed: R60.2, U6.45
unnamed: R61.1, R62.2, U6.40
unnamed: R84.1, R99.2
unnamed: R107.1, U10.3
unnamed: R117.1, R118.2, R122.2
unnamed: R124.1, R125.2, R127.2
unnamed: R143.1, U16.L8
unnamed: R145.1, U17.L8
unnamed: R156.1, U18.12
unnamed: R185.1, U1.D14
unnamed: R186.1, U1.H5
unnamed: R187.1, U1.G5
unnamed: R188.2, U1.F4
unnamed: R189.2, U1.D4
unnamed: R190.2, U1.E4
unnamed: R191.2, U1.G4
unnamed: R192.2, U1.F5
unnamed: R193.2, U1.J4
unnamed: R194.2, U1.K1
unnamed: R195.2, U1.K4
unnamed: R196.2, U1.L4
unnamed: R197.2, U1.L1
unnamed: R198.2, U1.M4
unnamed: R199.2, U1.K3
unnamed: R200.2, U1.M3
unnamed: R201.2, U1.K2
unnamed: R202.2, U1.N2
unnamed: R203.2, U1.J5
unnamed: R204.2, U1.R4
unnamed: R205.2, U1.L5
unnamed: R206.2, U1.P4
unnamed: R207.2, U1.P5
unnamed: R208.2, U1.N1
unnamed: R209.2, U1.M5
unnamed: R210.2, U1.N3
unnamed: R212.2, U1.N5
unnamed: U2.4, Y1.2
unnamed: U2.5, Y1.1
unnamed: U2.6, Y1.3
unnamed: U2.7, Y1.4
unnamed: U4.14, U5.1
PG_ALL: C119#2.1, D5.1, Q2.1, R45.1, U6.20
V1P2: C181.1, C183.1, C184.1, C185.1, C186.1, C187.1, C189.1, C191.1, C193.1, C195.1, C196.1, C198.1, FB4.1, FB5.1, FB6.1, L7.1, U10.4
V3P3: C176.1, C182.1, C200.1, C201.1, C206.1, C207.1, C213.1, C214.1, C215.1, C216.1, C217.1, C218.1, C219.1, C220.1, C221.1, C222.1, C223.1, C224.1, C225.1, C226.1, C227.1, C228.1, C229.1, C230.1, C231.1, C232.1, C233.1, C234.1, C235.1, C236.1, FB7.2, IC7.8, IC9.D2, IC9.D6, IC9.E3, IC9.E5, IC9.F2, IC9.F6, IC9.G3, IC9.G5, IC9.H2, IC9.H6, IC9.J3, IC9.J5, IC9.K2, IC9.K6, IC9.L3, IC9.L5, IC9.M2, IC9.M6, IC9.N3, IC9.N5, IC9.P2, IC9.P6, R101.1, R103.1, R104.1, R113.1, R114.1, R115.1, TP2.1, U9.2, U9.4
VCC1V0: C14.1, C21.1, C28.1, C35.1, C48.1, C53.1, C58.1, C63.1, C67.1, C71.1, R67.1, U1.G11, U1.G13, U1.H10, U1.H12, U1.J13, U1.K12, U1.L13, U1.M12, U1.N13, U1.P12, U1.R13, U6.14
VCC1V8: C5.1, C7.1, C9.1, C11.1, C16.1, C18.1, C23.1, C25.1, C30.1, C32.1, C37.1, C39.1, C47.1, C52.1, C57.1, C62.1, C80.1, C92.1, C93.1, C94.1, C99.1, C104.1, C105.1, C106.1, C107.1, C108.1, C144.1, C332.1, C335.1, FB1.2, FB14.2, IC1.5, IC2.11, IC2.28, IC2.30, IC2.32, L4.1, R1.1, R4.1, R5.2, R6.1, R13.1, R15.1, R16.1, R18.1, R19.1, R25.1, R43.2, R56.1, R64.2, R109.2, R153.2, U1.A13, U1.B16, U1.D12, U1.E15, U1.F8, U1.G9, U1.H8, U1.J11, U1.K8, U1.L11, U1.M8, U1.N9, U1.N11, U1.P10, U1.R9, U2.18, U2.21, U2.23, U2.26, U2.29, U2.32, U2.34, U2.39, U2.40
VCC1V35: C4.1, C8.1, C12.1, C13.1, C19.1, C20.1, C26.1, C27.1, C33.1, C34.1, C40.1, C41.1, C143.1, C290.1, C291.1, C293.1, C294.1, C295.1, C296.1, C297.2, C298.1, C299.1, C300.1, C301.1, C302.1, C303.1, C304.1, C305.1, C306.1, C307.1, C308.1, C309.1, C310.1, C311.1, C312.1, C313.1, C314.1, C315.1, C316.1, C317.1, C318.1, C319.1, C320.1, C321.1, C322.1, C323.1, C324.1, C325.1, C326.1, C327.1, C328.1, C329.1, C331.2, L3.1, R60.1, R63.2, R187.2, U1.A3, U1.D2, U1.E5, U1.G1, U1.H4, U1.L3, U1.P2, U1.R5, U1.U1, U1.V4, U16.A1, U16.A8, U16.B2, U16.C1, U16.C9, U16.D2, U16.D9, U16.E9, U16.F1, U16.G7, U16.H2, U16.H9, U16.K2, U16.K8, U16.N1, U16.N9, U16.R1, U16.R9, U17.A1, U17.A8, U17.B2, U17.C1, U17.C9, U17.D2, U17.D9, U17.E9, U17.F1, U17.G7, U17.H2, U17.H9, U17.K2, U17.K8, U17.N1, U17.N9, U17.R1, U17.R9
VCC2V5: C49.1, C54.1, C59.1, C64.1, C68.1, C72.1, C75.1, C269.1, C272.1, C277.1, C280.1, C285.1, C288.1, FB9.1, FB11.1, FB13.1, IC11.30, IC11.31, IC12.30, IC12.31, IC13.30, IC13.31, L9.2, L10.2, R134.1, R137.1, R140.1, U1.T8, U1.U11, U1.W7, U1.Y10
VCC3V3: C1.1, C2.1, C3.1, C6.1, C10.1, C15.1, C17.1, C22.1, C24.1, C29.1, C31.1, C36.1, C38.1, C44.1, C45.1, C46.1, C50.1, C51.1, C55.1, C56.1, C60.1, C61.1, C65.1, C66.1, C69.1, C70.1, C73.1, C74.1, C76.1, C77.1, C78.1, C79.1, C91.1, C114.2, C116.1, C121.1, C124.1, C126.1, C241.1, C242.1, C243.1, C244.1, C245.1, C246.1, C339.1, C343.1, C346.1, C392.2, D5.3, D6.2, D11.2, IC1.21, IC3.8, IC4.3, IC14.A3, IC14.A4, IC14.A5, IC14.E7, IC18.16, J1.4, J2.6, J15.1, J16.1, J17.1, J18.1, L8.2, R3.1, R9.1, R10.1, R11.1, R30.2, R35.1, R36.1, R37.1, R38.1, R39.1, R45.2, R66.1, R108.2, R146.1, U1.B6, U1.C19, U1.D7, U1.F18, U1.G7, U1.H14, U1.J7, U1.J17, U1.K6, U1.K20, U1.L7, U1.M6, U1.M16, U1.N6, U1.N7, U1.N19, U1.P8, U1.R6, U1.R7, U1.R15, U1.T6, U1.T18, U1.V14, U1.W17, U1.Y20, U2.8, U2.9, U4.2, U6.8, U13.3, U13.6, U13.7, U14.2, U14.10, U14.19, U15.2, U15.10, U15.19
VCC5V: C384.1, IC16.8, R164.1, R181.2, R182.2
VCC5V0: C110.1, C171.1, FB3.2, FB8.1, FB10.1, FB12.1, IC6.10, J19.5, L6.1, R41.2, R82.1, U3.5
VCCPLL: C42.1, C43.1, FB1.1, U1.G8
VIO: C202.1, C203.1, C205.1, C208.1, C209.1, C211.1, C212.1, R84.2, R85.2, R108.1, R109.1, TP3.1
XADC1V8: C82.1, C145.1, R57.1, U1.J9, U6.7
XADC1V25: C81.1, C133.1, IC4.4, U1.L9

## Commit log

2021-01-14 Added branch V1
2021-01-14 The initial commi
2021-01-14 The 2nd commit
2021-01-15 Created the project library and add CYUSB3014 usb controller
2021-01-17 Added FPGA xa7z020-1clg400 to the library
2021-01-17 add footprint for FPGA xa7z020-1clg400
2021-01-19 Added ADC LTC2387CUH-18 and DAC LTC1668CG to the project library
2021-01-21 Added SDRAM_AS4C256M16D3LC-12BCN to the project library
2021-01-21 Added POWER_ADP5052ACPZ-R7 to the project library
2021-01-24 Removed README.md and desktop.ini from project folder
2021-01-26 added LevelTranslator_TXS02612RTWR to the library
2021-01-26 added MicroSDcard_1040310811 to the library
2021-01-26 Modified footprint of MicroSDcard_1040310811 and added ETHERNET CONN_RJMG2012211A0FR
2021-01-26 Added ETHERNET PHY_DP83869HMRGZT to the library
2021-01-27 Added RTC_DS3231S to the library
2021-02-02 Deleted all files
2021-02-02 Created the project again
2021-02-03 Added other sheets
2021-02-04 Power_Supply Sch partially completed
2021-02-05 Added parts to the FPGA_Power
2021-02-05 EEPROM schematics were drawn
2021-02-06 Completeed the FPGA_Power sheet Created PCB
2021-02-07 Added power symbol to EEPROM sheet
2021-02-09 Drawn schematic of RTC
2021-02-09 Added battery holder to the RTC clock
2021-02-10 Added new power sheet for 48V-12V converter
2021-02-11 Added fan control circuitry
2021-02-11 Added new sheet for Ethernet PHY Connector and drawn schematic (continue)
2021-02-11 Added USB SRAM sheet,Added USB3 ethernet ic
2021-02-12 Drawn Ethernet PHY schematic (continue...)
2021-02-12 Added clock gen parts
2021-02-13 Drawn Eth power schematics and Eth PHY (continue)
2021-02-14 Drawn Ethernet PHY schematics
2021-02-14 Drawn configuration cct of Ethernet PHY Drawn Clock Gen cct
2021-02-15 Completed power 48v to 12v sheet
2021-02-16 Completed ETH conn net connections
2021-02-17 Added relevant main components to the sheet USB2.sch sheet
2021-02-17 Drawn USB2 schematics
2021-02-18 Completed USB3 1.2V Added 5V regulator cct partially completed Added BTB connector
2021-02-20 Corrected Eth conn connections
2021-02-20 Modified LED nets and JTag nets of ETH schematic
2021-02-20 Added USB3 SRAM Added 5V regulator
2021-02-20 Added USB3 type B connector Added ESD protection to the same sheet
2021-02-21 Completed FPGA power sheet completed USB3 completed FPGA config
2021-02-22 Drawn schematic RAM
2021-02-23 Added sheet Ext_Analog
2021-02-23 Completed LED_Comm Completed Ext_Analog Added AWG and ADC sheets
2021-02-24 Added bus lines -ETH_PHY_CONN -RAM -USB2 Made Output the port direction of clkout of Clock_Gen Placed sheet entris of sheet symbols on top sheet
2021-02-26 Added new sheet RS232_Port Drawn the schematics RS232_Port
2021-02-26 Added Sheet FPGA_Banks Drawn the connections of FPGA and RAM Completed the top sheet connections
2021-02-26 Rearranged the top sheet blocks modified hir. pins in few blocks
2021-02-27 Added nets for fx3 usb3 cct from fpga
2021-02-27 Connected USB2 connections with FPGA and updated the top sheet
2021-03-04 Added ADC, DAC ,Clock pins to FPGA_Banks
2021-03-05 Added ADC schematic
2021-03-07 Changed Bank13 deoupling caps and set the bank voltage to 2.5V
2021-03-15 Added Fast DAC schematic
2021-03-17 Connected Ethernet sheet with FPGA bank
2021-03-18 -Clock --GND pin was missing. it was added to pin 45 -BTB --pins added
2021-03-19 PCB created and schematics annotated High speed connections added to the BTB
2021-03-21 BTB and FPGA pins added and connections were made
2021-03-23 Connections were made to FPGA banks
2021-03-27 Corrected PCB import errors
